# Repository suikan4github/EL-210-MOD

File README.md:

# EL-210-MOD
Alternative circuit for SHARP EL-210/EL-215 calculator

# Description

This is a circuit/board design for the alternate PCB for the SHARP EL-210/215 calculators. SHARP EL-210 series are manufactured around early 1980th. 
By using this alternate PCB, you can program any program as firmware of this
classic VFD calculator. 

There is an dedicated RPN firmware is located in the [rpn2026](https://github.com/suikan4github/rpn2026) project.

To make your own RPN calculator,
user must follow the procedure : 
1. Take the main board of the EL-210 out. 
1. Move the VFD from the old board to this board. 
1. Set this board into the EL-210 calculator. 
1. Program the board with the appropriate RPN firmware. 

# Circuit Design

You can found additional design resources : 
- [Schematic diagram](doc/EL-210-MOD.pdf).
- [Parts list](doc/partslist.csv).

## VFD specification
The VFD is 9-ST-20, manufactured by Futaba. The specification is not disclosed. 
Pin assignment has been investigated by [LI2026ODP](https://github.com/suikan4github/LI2026ODP/wiki/LI2026A) project.
- Anode voltage : 25V
- Heater voltage : 2.5v (Differential square wave drive), 21mA. 
- Grid cutoff : 4V

## Heater driver
The heater must be driven by differential alternate current. This is required to make the flat brightness between right-end and left-end of the VFD. If you drive 
the heater by DC, the voltage slope of the heater will make the slop of the brightness.

The analog switch provide the low voltage drop out current switching. The timing
is made by MCU timer.

## Grid bias 
The grid bias is required 4. Because the balanced drive of the heater makes
1.65V grid bias, we need only 2.5V more. 

## Key matrix
The key matrix has been investigated by also [LI2026ODP](https://github.com/suikan4github/LI2026ODP/wiki/KeyMatrix) project. 

The EL-21x series key matrix doesn't have any protection diode. Thus, to prevent the signal shortage,
the GPIO pins for the key matrix have to be configured : 
- Row : Open Drain output.
- Col : Input with pull-up register. 

To check the button pushed, output the "L" from the Row.
If the Column get "L", the button is pushed. 

|  Row  | Column 0  |  Column 1  |  Column 2  |
| :---: | :---:     | :---:      | :---:      |
|   0   |   CE      |  X->M      |   0        |
|   1   |           |   7        |   4        |
|   2   |   CM      |   8        |   1        |
|   3   |   .       |   5        |   %        |
|   4   |   +       |   RM       |   2        |
|   5   |   C       |   9        |   =        |
|   6   |   /       |   M-       |            |
|   7   |   *       |   6        |   3        |
|   8   |   -       |   M+       |  sqrt      |

## 24V
To supply the 24V to VFD, set EN24 signal to "H".

# Caution
In the case you order the PCB to a board manufacturer, you must specify the 
PCB thinness as 1.0mm. The standard 1.3mm is too thick. 

# Known Problems
The Grid bias is not deep as expected. It is -0.9V while expected -2.5v. 
It is left untouched because it is not problematic. 

# Gallery

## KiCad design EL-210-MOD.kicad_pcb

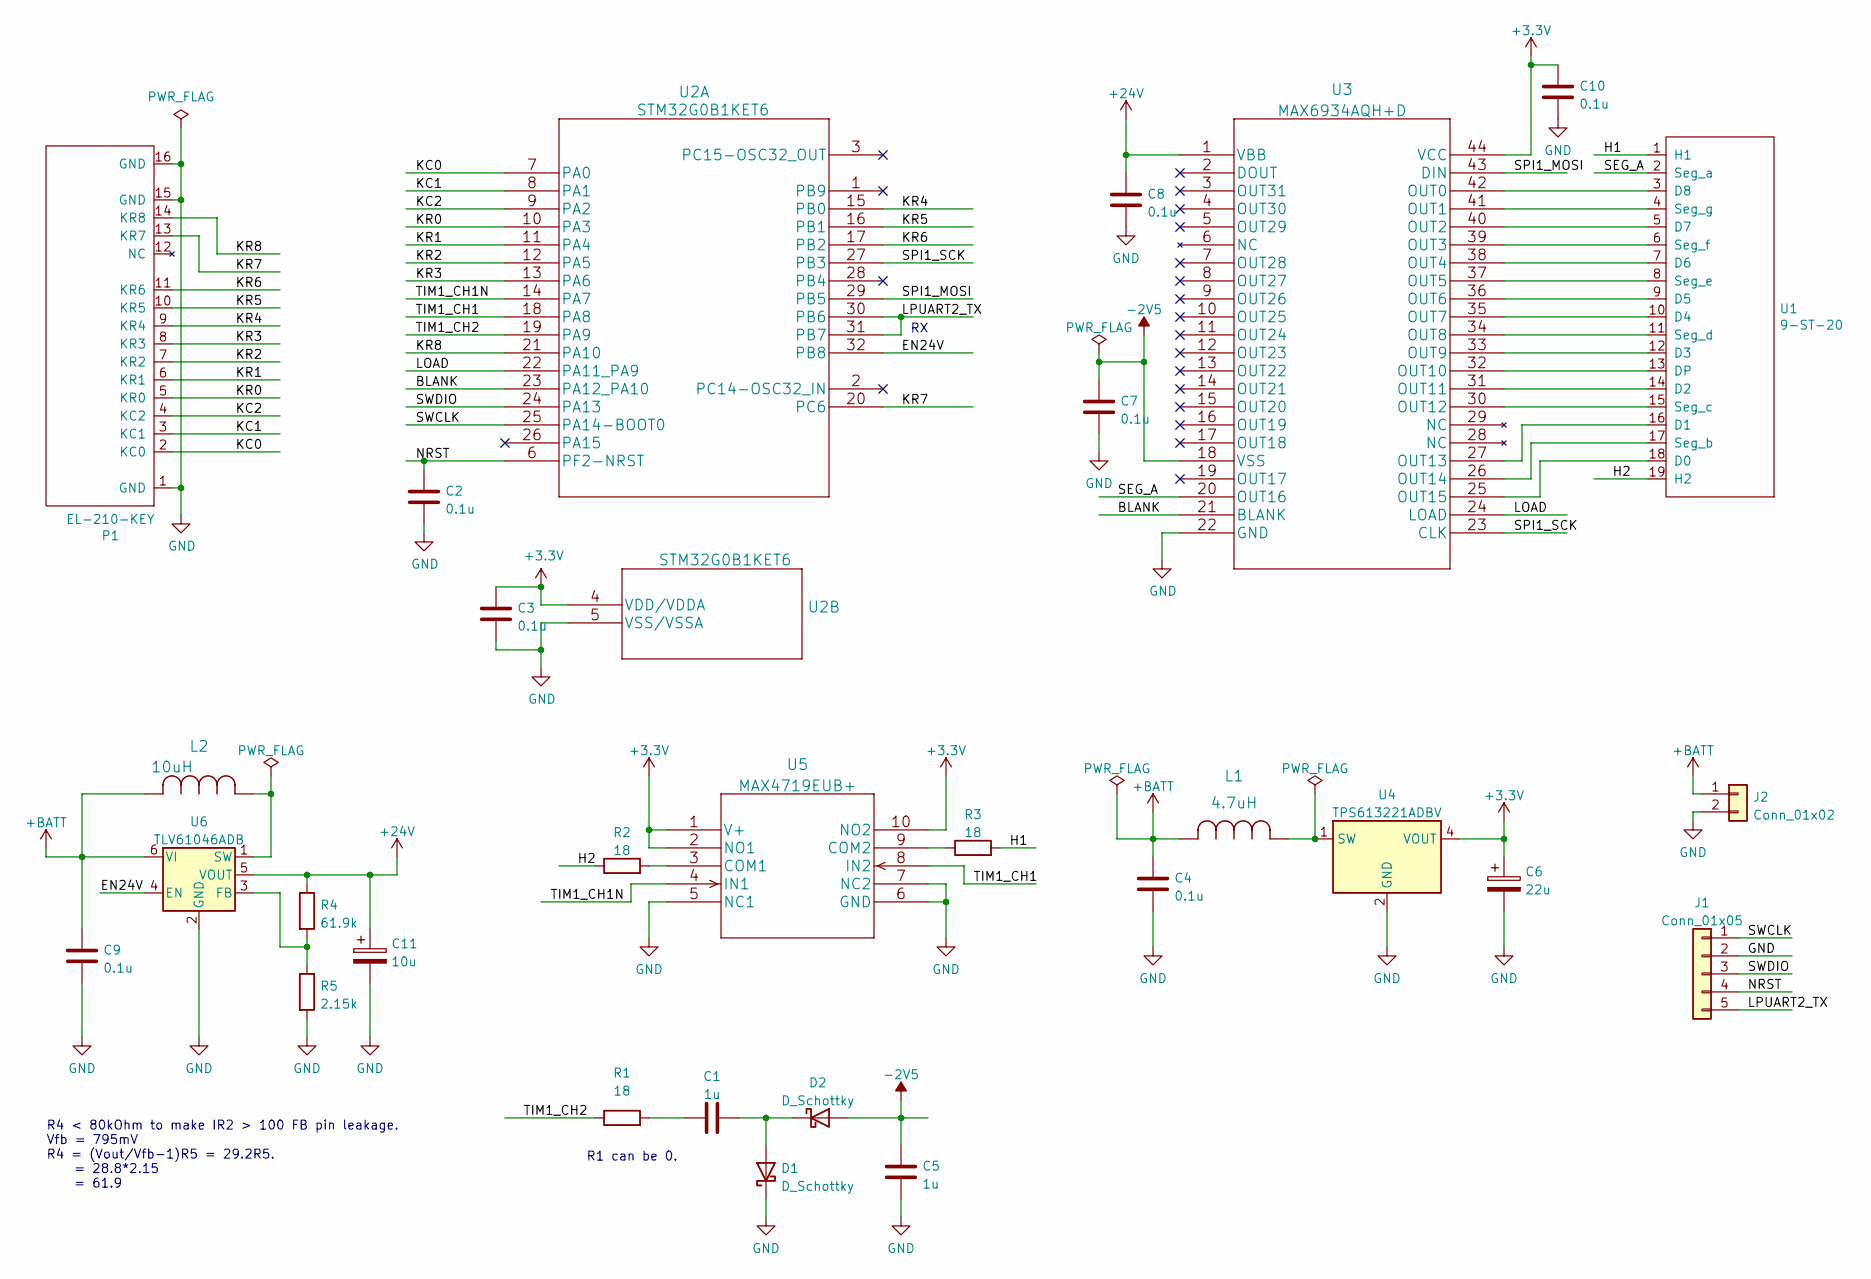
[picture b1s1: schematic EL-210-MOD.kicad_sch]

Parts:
C1, C5: 1u; C_0603_1608Metric_Pad1.08x0.95mm_HandSolder
C2, C3, C4, C7, C8, C9, C10: 0.1u; C_0603_1608Metric_Pad1.08x0.95mm_HandSolder
C6: 22u; CP_Elec_4x3.9
C11: 10u; CP_Elec_6.3x3.9
D1, D2: D_Schottky; D_0603_1608Metric_Pad1.05x0.95mm_HandSolder
J1: Conn_01x05; PinHeader_1x05_P2.54mm_Horizontal
J2: Conn_01x02; PinHeader_1x02_P2.54mm_Vertical
L1: 4.7uH; LQH5BPN100M38L
L2: 10uH; LQH5BPN100M38L
P1: EL-210-KEY
R1, R2, R3: 18; R_0603_1608Metric_Pad0.98x0.95mm_HandSolder
R4: 61.9k; R_0603_1608Metric_Pad0.98x0.95mm_HandSolder
R5: 2.15k; R_0603_1608Metric_Pad0.98x0.95mm_HandSolder
U1: 9-ST-20
U2: STM32G0B1KET6; LQFP-32_7x7mm_P0.8mm
U3: MAX6934AQH+D; PLCC44_handsoldering
U4: TPS613221ADBV; SOT-23-5
U5: MAX4719EUB+; MSOP-10_3x3mm_P0.5mm
U6: TLV61046ADB; SOT-23-6

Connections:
+3V3: C3.2, C6.1, C10.1, U2.4 (VDD/VDDA), U3.44 (VCC), U4.4 (VOUT), U5.1 (V+), U5.2 (NO1), U5.10 (NO2)
+24V: C8.1, C11.1, R4.1, U3.1 (VBB), U6.5 (VOUT)
+BATT: C4.1, C9.1, J2.1, L1.2, L2.2, U6.6 (VI)
-2V5: C5.1, C7.1, D2.2 (A), U3.18 (VSS)
/BLANK: U2.23 (PA12_PA10), U3.21 (BLANK)
/EN24V: U2.32 (PB8), U6.4 (EN)
/H1: R3.2, U1.1 (H1)
/H2: R2.1, U1.19 (H2)
/KC0: P1.2 (KC0), U2.7 (PA0)
/KC1: P1.3 (KC1), U2.8 (PA1)
/KC2: P1.4 (KC2), U2.9 (PA2)
/KR0: P1.5 (KR0), U2.10 (PA3)
/KR1: P1.6 (KR1), U2.11 (PA4)
/KR2: P1.7 (KR2), U2.12 (PA5)
/KR3: P1.8 (KR3), U2.13 (PA6)
/KR4: P1.9 (KR4), U2.15 (PB0)
/KR5: P1.10 (KR5), U2.16 (PB1)
/KR6: P1.11 (KR6), U2.17 (PB2)
/KR7: P1.13 (KR7), U2.20 (PC6)
/KR8: P1.14 (KR8), U2.21 (PA10)
/LOAD: U2.22 (PA11_PA9), U3.24 (LOAD)
/LPUART2_TX: J1.5, U2.30 (PB6), U2.31 (PB7)
/NRST: C2.1, J1.4, U2.6 (PF2-NRST)
/SEG_A: U1.2 (Seg_a), U3.20 (OUT16)
/SPI1_MOSI: U2.29 (PB5), U3.43 (DIN)
/SPI1_SCK: U2.27 (PB3), U3.23 (CLK)
/SWCLK: J1.1, U2.25 (PA14-BOOT0)
/SWDIO: J1.3, U2.24 (PA13)
/TIM1_CH1: U2.18 (PA8), U5.8 (IN2)
/TIM1_CH1N: U2.14 (PA7), U5.4 (IN1)
/TIM1_CH2: R1.1, U2.19 (PA9)
GND: C2.2, C3.1, C4.2, C5.2, C6.2, C7.2, C8.2, C9.2, C10.2, C11.2, D1.1 (K), J1.2, J2.2, P1.1 (GND), P1.15 (GND), P1.16 (GND), R5.2, U2.5 (VSS/VSSA), U3.22 (GND), U4.2 (GND), U5.5 (NC1), U5.6 (GND), U5.7 (NC2), U6.2 (GND)
unnamed: C1.1, R1.2
unnamed: C1.2, D1.2 (A), D2.1 (K)
unnamed: L1.1, U4.1 (SW)
unnamed: L2.1, U6.1 (SW)
unnamed: R2.2, U5.3 (COM1)
unnamed: R3.1, U5.9 (COM2)
unnamed: R4.2, R5.1, U6.3 (FB)
unnamed: U1.3 (D8), U3.42 (OUT0)
unnamed: U1.4 (Seg_g), U3.41 (OUT1)
unnamed: U1.5 (D7), U3.40 (OUT2)
unnamed: U1.6 (Seg_f), U3.39 (OUT3)
unnamed: U1.7 (D6), U3.38 (OUT4)
unnamed: U1.8 (Seg_e), U3.37 (OUT5)
unnamed: U1.9 (D5), U3.36 (OUT6)
unnamed: U1.10 (D4), U3.35 (OUT7)
unnamed: U1.11 (Seg_d), U3.34 (OUT8)
unnamed: U1.12 (D3), U3.33 (OUT9)
unnamed: U1.13 (DP), U3.32 (OUT10)
unnamed: U1.14 (D2), U3.31 (OUT11)
unnamed: U1.15 (Seg_c), U3.30 (OUT12)
unnamed: U1.16 (D1), U3.27 (OUT13)
unnamed: U1.17 (Seg_b), U3.26 (OUT14)
unnamed: U1.18 (D0), U3.25 (OUT15)

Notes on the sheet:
R4 < 80kOhm to make IR2 > 100 FB pin leakage. Vfb = 795mV R4 = (Vout/Vfb-1)R5 = 29.2R5. = 28.8*2.15 = 61.9
R1 can be 0.

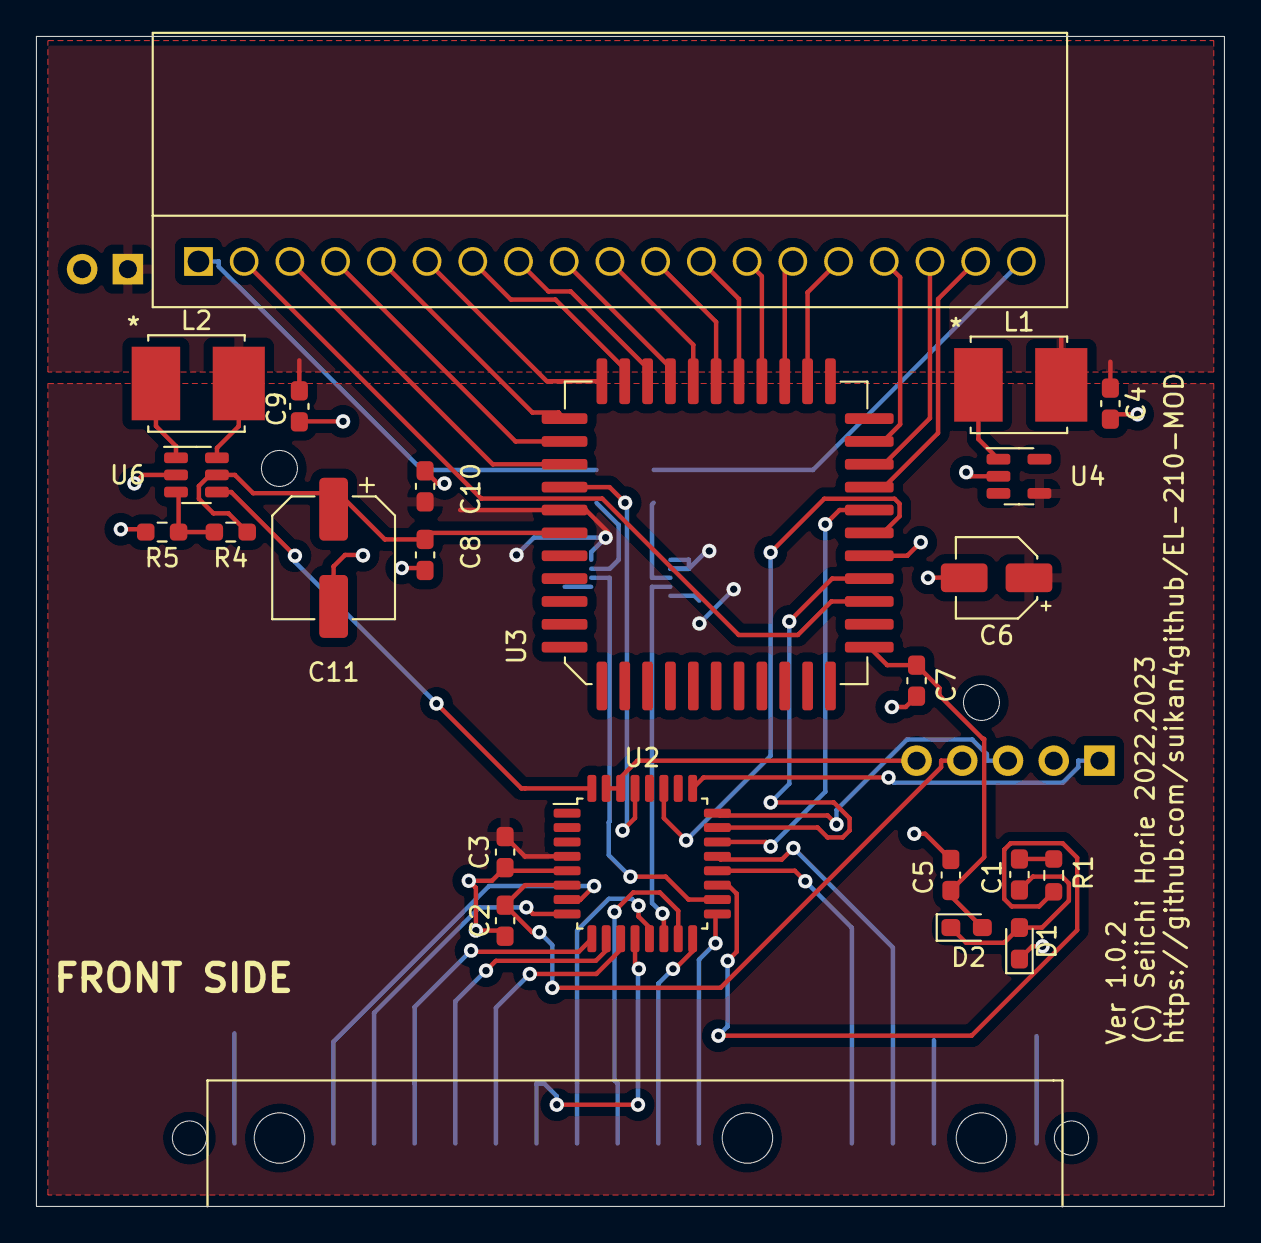
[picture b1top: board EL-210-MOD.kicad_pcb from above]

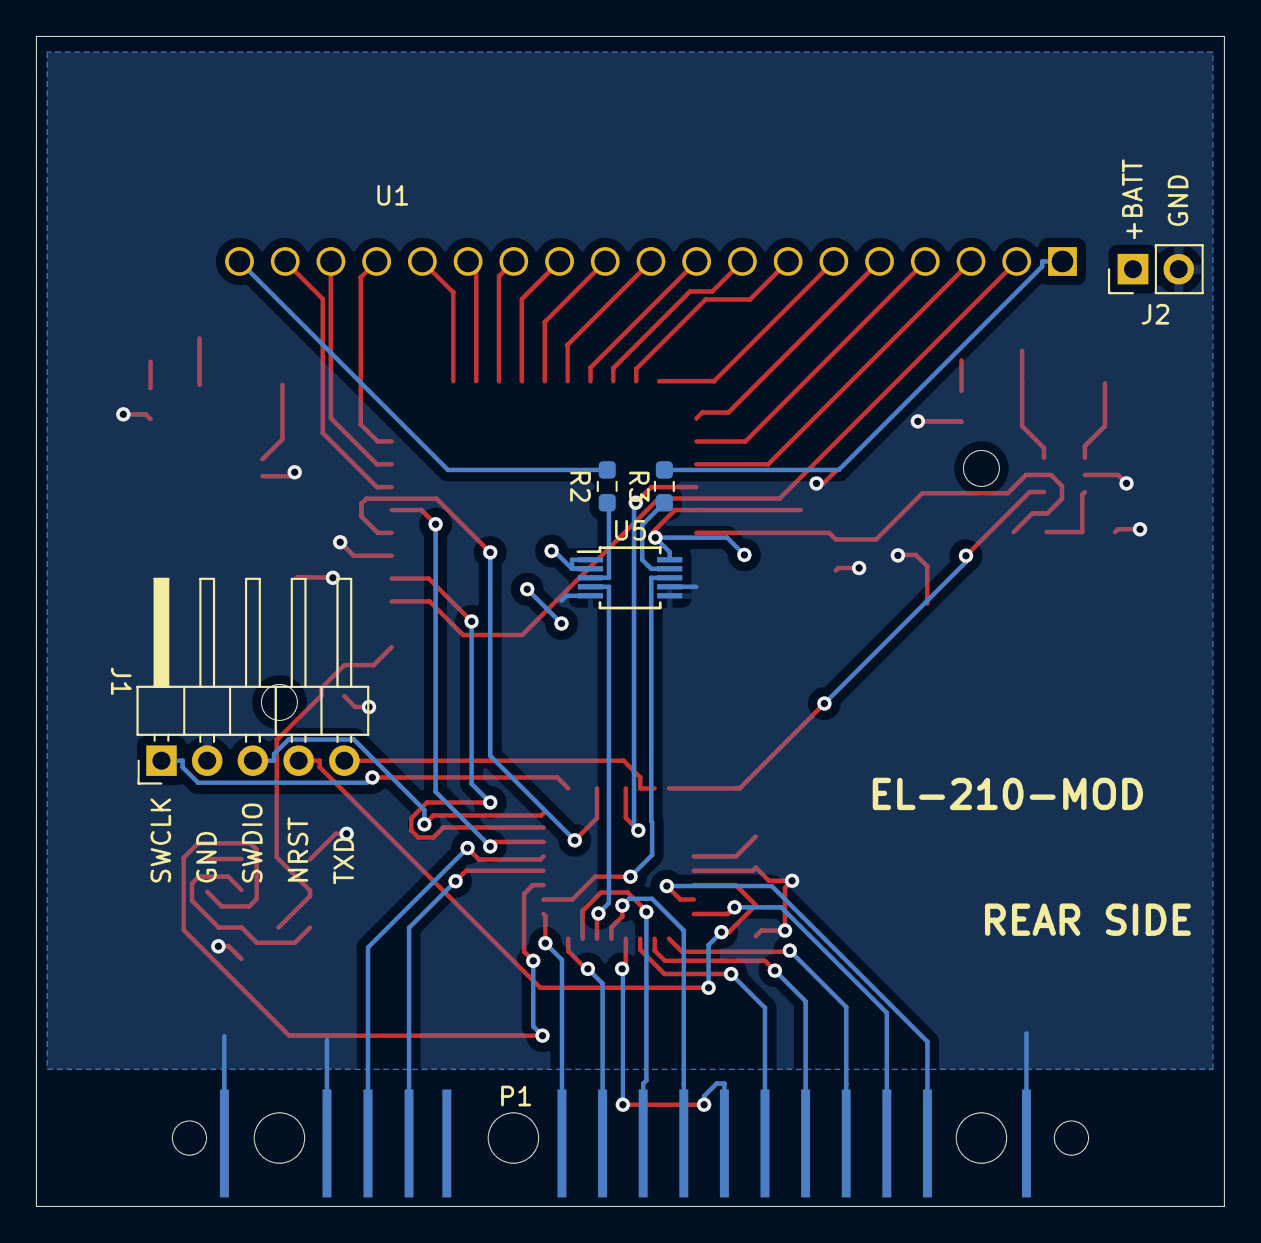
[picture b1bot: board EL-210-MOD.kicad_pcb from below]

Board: 2 copper layers, 66.0 x 65.0 mm, 36 parts (5 on the bottom side), 55 nets.

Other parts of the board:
H1, H2: hole_2.0mm
H3, H7: hole_1.9mm; hole_1.8mm
H4, H5, H6: hole_2.8mm

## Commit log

2022-11-12 Board layout copied from Akashi-10
2022-11-13 Add project symbol and footprint
2022-11-15 Rough layout of the digital part.
2022-11-15 Add analog parts.
    Waiting for SWD port.
2022-11-21 Schematics is finished.
2022-11-21 Change PLCC footprint to handsolder type
2022-11-23 parts placed.
    The version number is written.
    The SMD pad of the Ls are modifed.
    Routing is not finished.
2022-11-23 Schematics layout refined.
    Added note on the Tc and R4/R5 expression.
2022-11-23 Layout refined.
    Higher parts are moved to the front side to avoid the
    touch with the back cabinet.
2022-11-27 Layout finished.
    DRC passed except silkscreen minor problem.
2022-12-11 Gerber file generated
2023-01-09 Corrected signal name from TIM2_CH1 to TIM1_CH2
    Fixed typo. Layout is not changed.
2023-01-11 Update schematics.
    - Change the key matrix signal name.
    -- Including the re-order of the Key row.
    - Change the value of the R1 from 330 to 18.
    - Schematic is generatd in PDF.
    - Layout is generated in gerber.
2023-01-23 Refresh the layout.
    Regenerated the gerber for v1.0.1
2023-01-23 Update .gitignore
    gerber file is excluded.
2023-02-12 Fixed foot print of the C6 and C11.
    The foot prints of those capacitor was wrong.
    Corrected them.
2023-02-12 Added image
2023-03-11 Update images.
2024-02-23 Fixed link to the schematics.

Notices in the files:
parts and their libraries:
Copyright 2021 Accelerated Designs. All rights reserved.
